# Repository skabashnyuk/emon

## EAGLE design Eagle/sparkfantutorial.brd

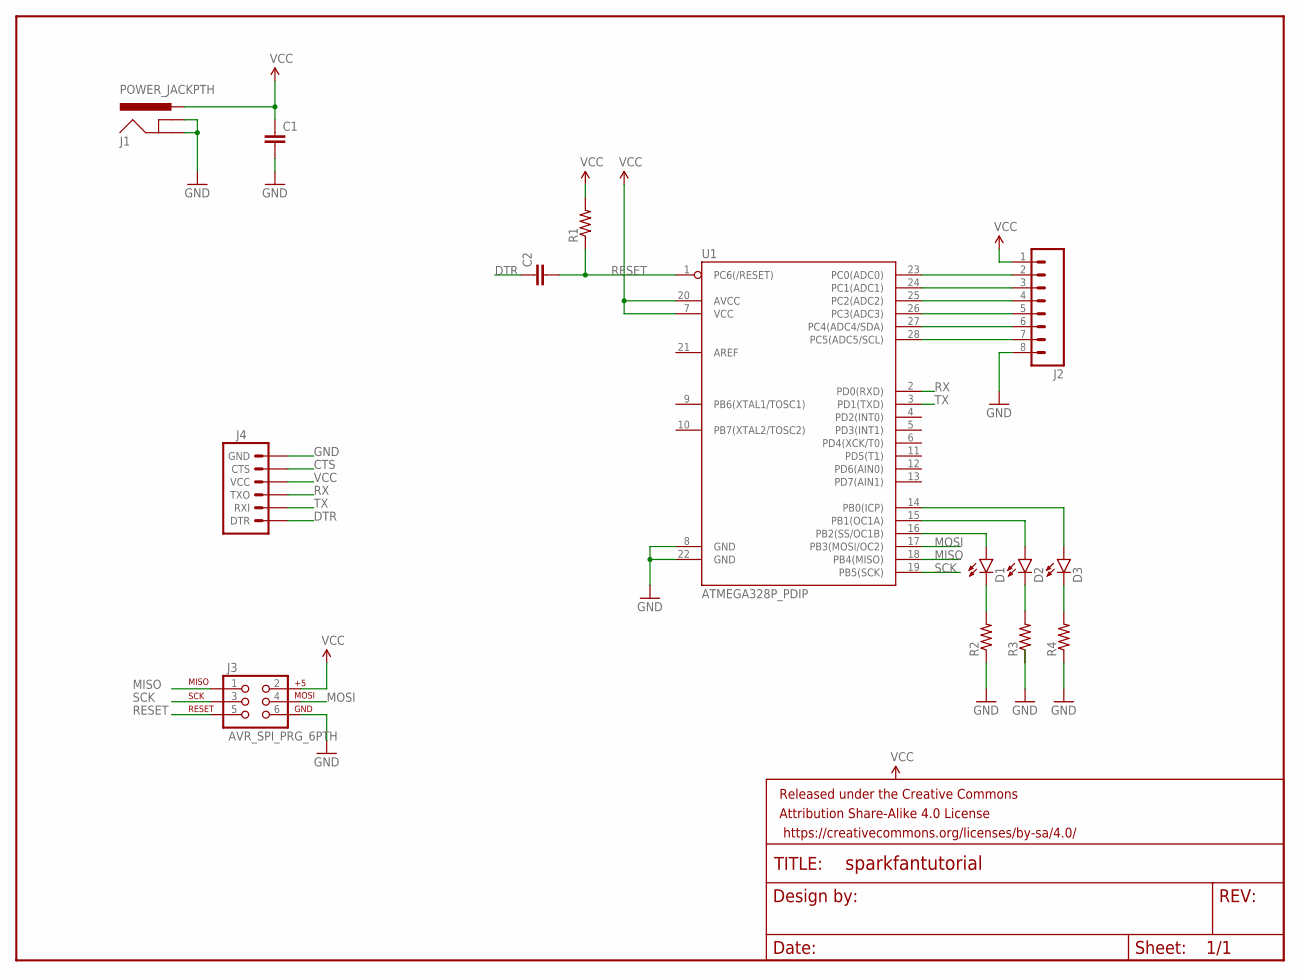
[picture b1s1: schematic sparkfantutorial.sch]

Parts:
C1, C2: CAPPTH; CAP-PTH-SMALL
D1, D2, D3: LED5MM
FRAME1: FRAME-LETTER; CREATIVE_COMMONS
J1: POWER_JACKPTH; POWER_JACK_PTH
J2: M08; 1X08_ROUND
J3: AVR_SPI_PRG_6PTH; 2X3
J4: ARDUINO_SERIAL_PROGRAMPTH; 1X06
R1, R2, R3, R4: RESISTORPTH-1/4W; AXIAL-0.4
U1: ATMEGA328P_PDIP; DIL28-3

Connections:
CTS: J4.5 (CTS)
DTR: C2.1, J4.1 (DTR)
GND: C1.2, J1.GND, J1.GNDBREAK, J2.8, J3.6, J4.6 (GND), R2.P$1 (1), R4.P$1 (1), U1.8 (GND), U1.22 (GND)
MISO: J3.1, U1.18 (PB4(MISO))
MOSI: J3.4, U1.17 (PB3(MOSI/OC2))
unnamed: D1.K (C), R2.P$2 (2)
unnamed: D1.A, U1.16 (PB2(SS/OC1B))
unnamed: D2.A, U1.15 (PB1(OC1A))
unnamed: D3.A, U1.14 (PB0(ICP))
unnamed: J2.2, U1.23 (PC0(ADC0))
unnamed: J2.3, U1.24 (PC1(ADC1))
unnamed: J2.4, U1.25 (PC2(ADC2))
unnamed: J2.5, U1.26 (PC3(ADC3))
unnamed: J2.6, U1.27 (PC4(ADC4/SDA))
unnamed: J2.7, U1.28 (PC5(ADC5/SCL))
unnamed: D2.K (C), R3.P$2 (2)
unnamed: D3.K (C), R4.P$2 (2)
RESET: C2.2, J3.5, R1.P$1 (1), U1.1 (PC6(/RESET))
RX: J4.3 (TXO), U1.2 (PD0(RXD))
SCK: J3.3, U1.19 (PB5(SCK))
TX: J4.2 (RXI), U1.3 (PD1(TXD))
VCC: C1.1, J1.PWR, J2.1, J3.2, J4.4 (VCC), R1.P$2 (2), U1.7 (VCC), U1.20 (AVCC)

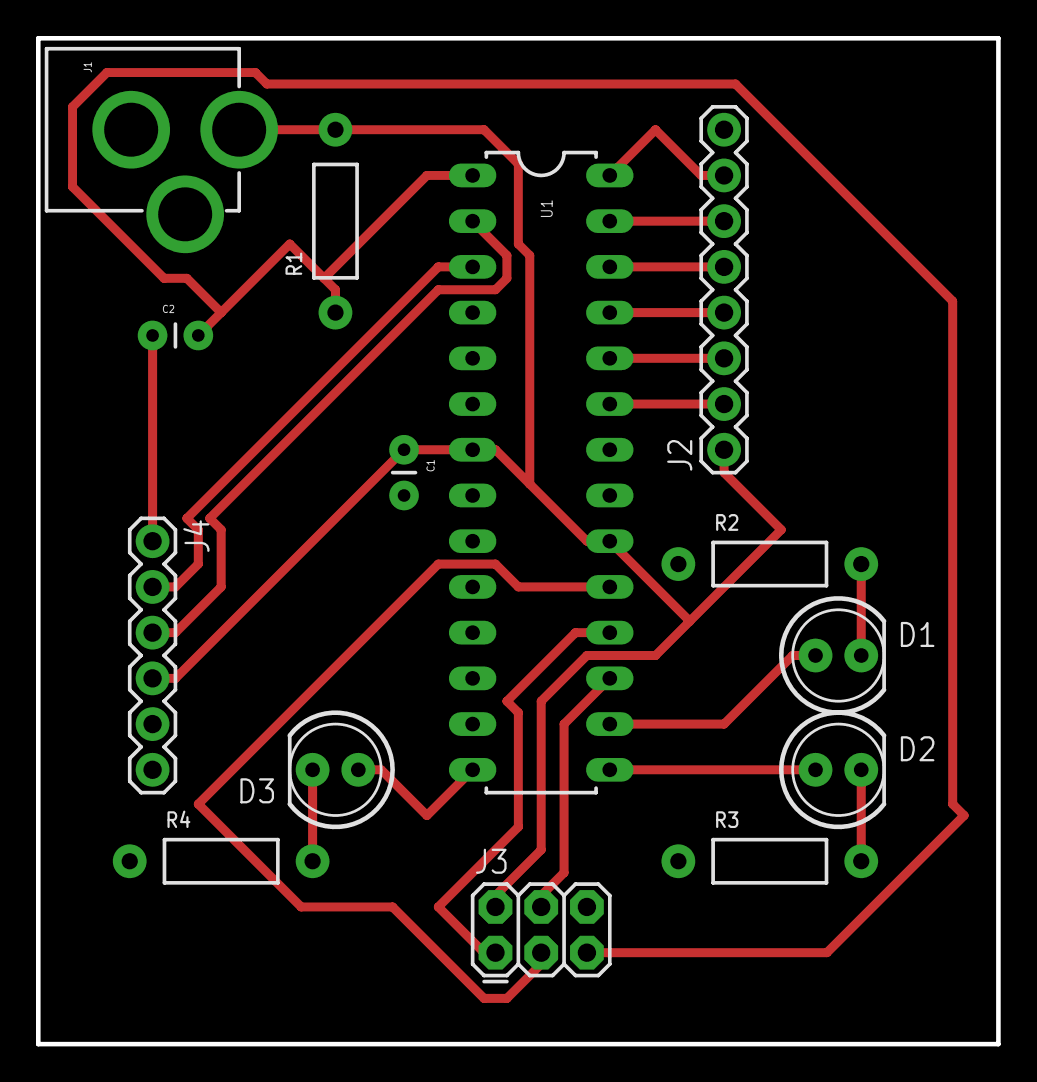
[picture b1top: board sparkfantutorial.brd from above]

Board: 2 copper layers, 53.3 x 55.9 mm, 15 parts (0 on the bottom side), 21 nets.

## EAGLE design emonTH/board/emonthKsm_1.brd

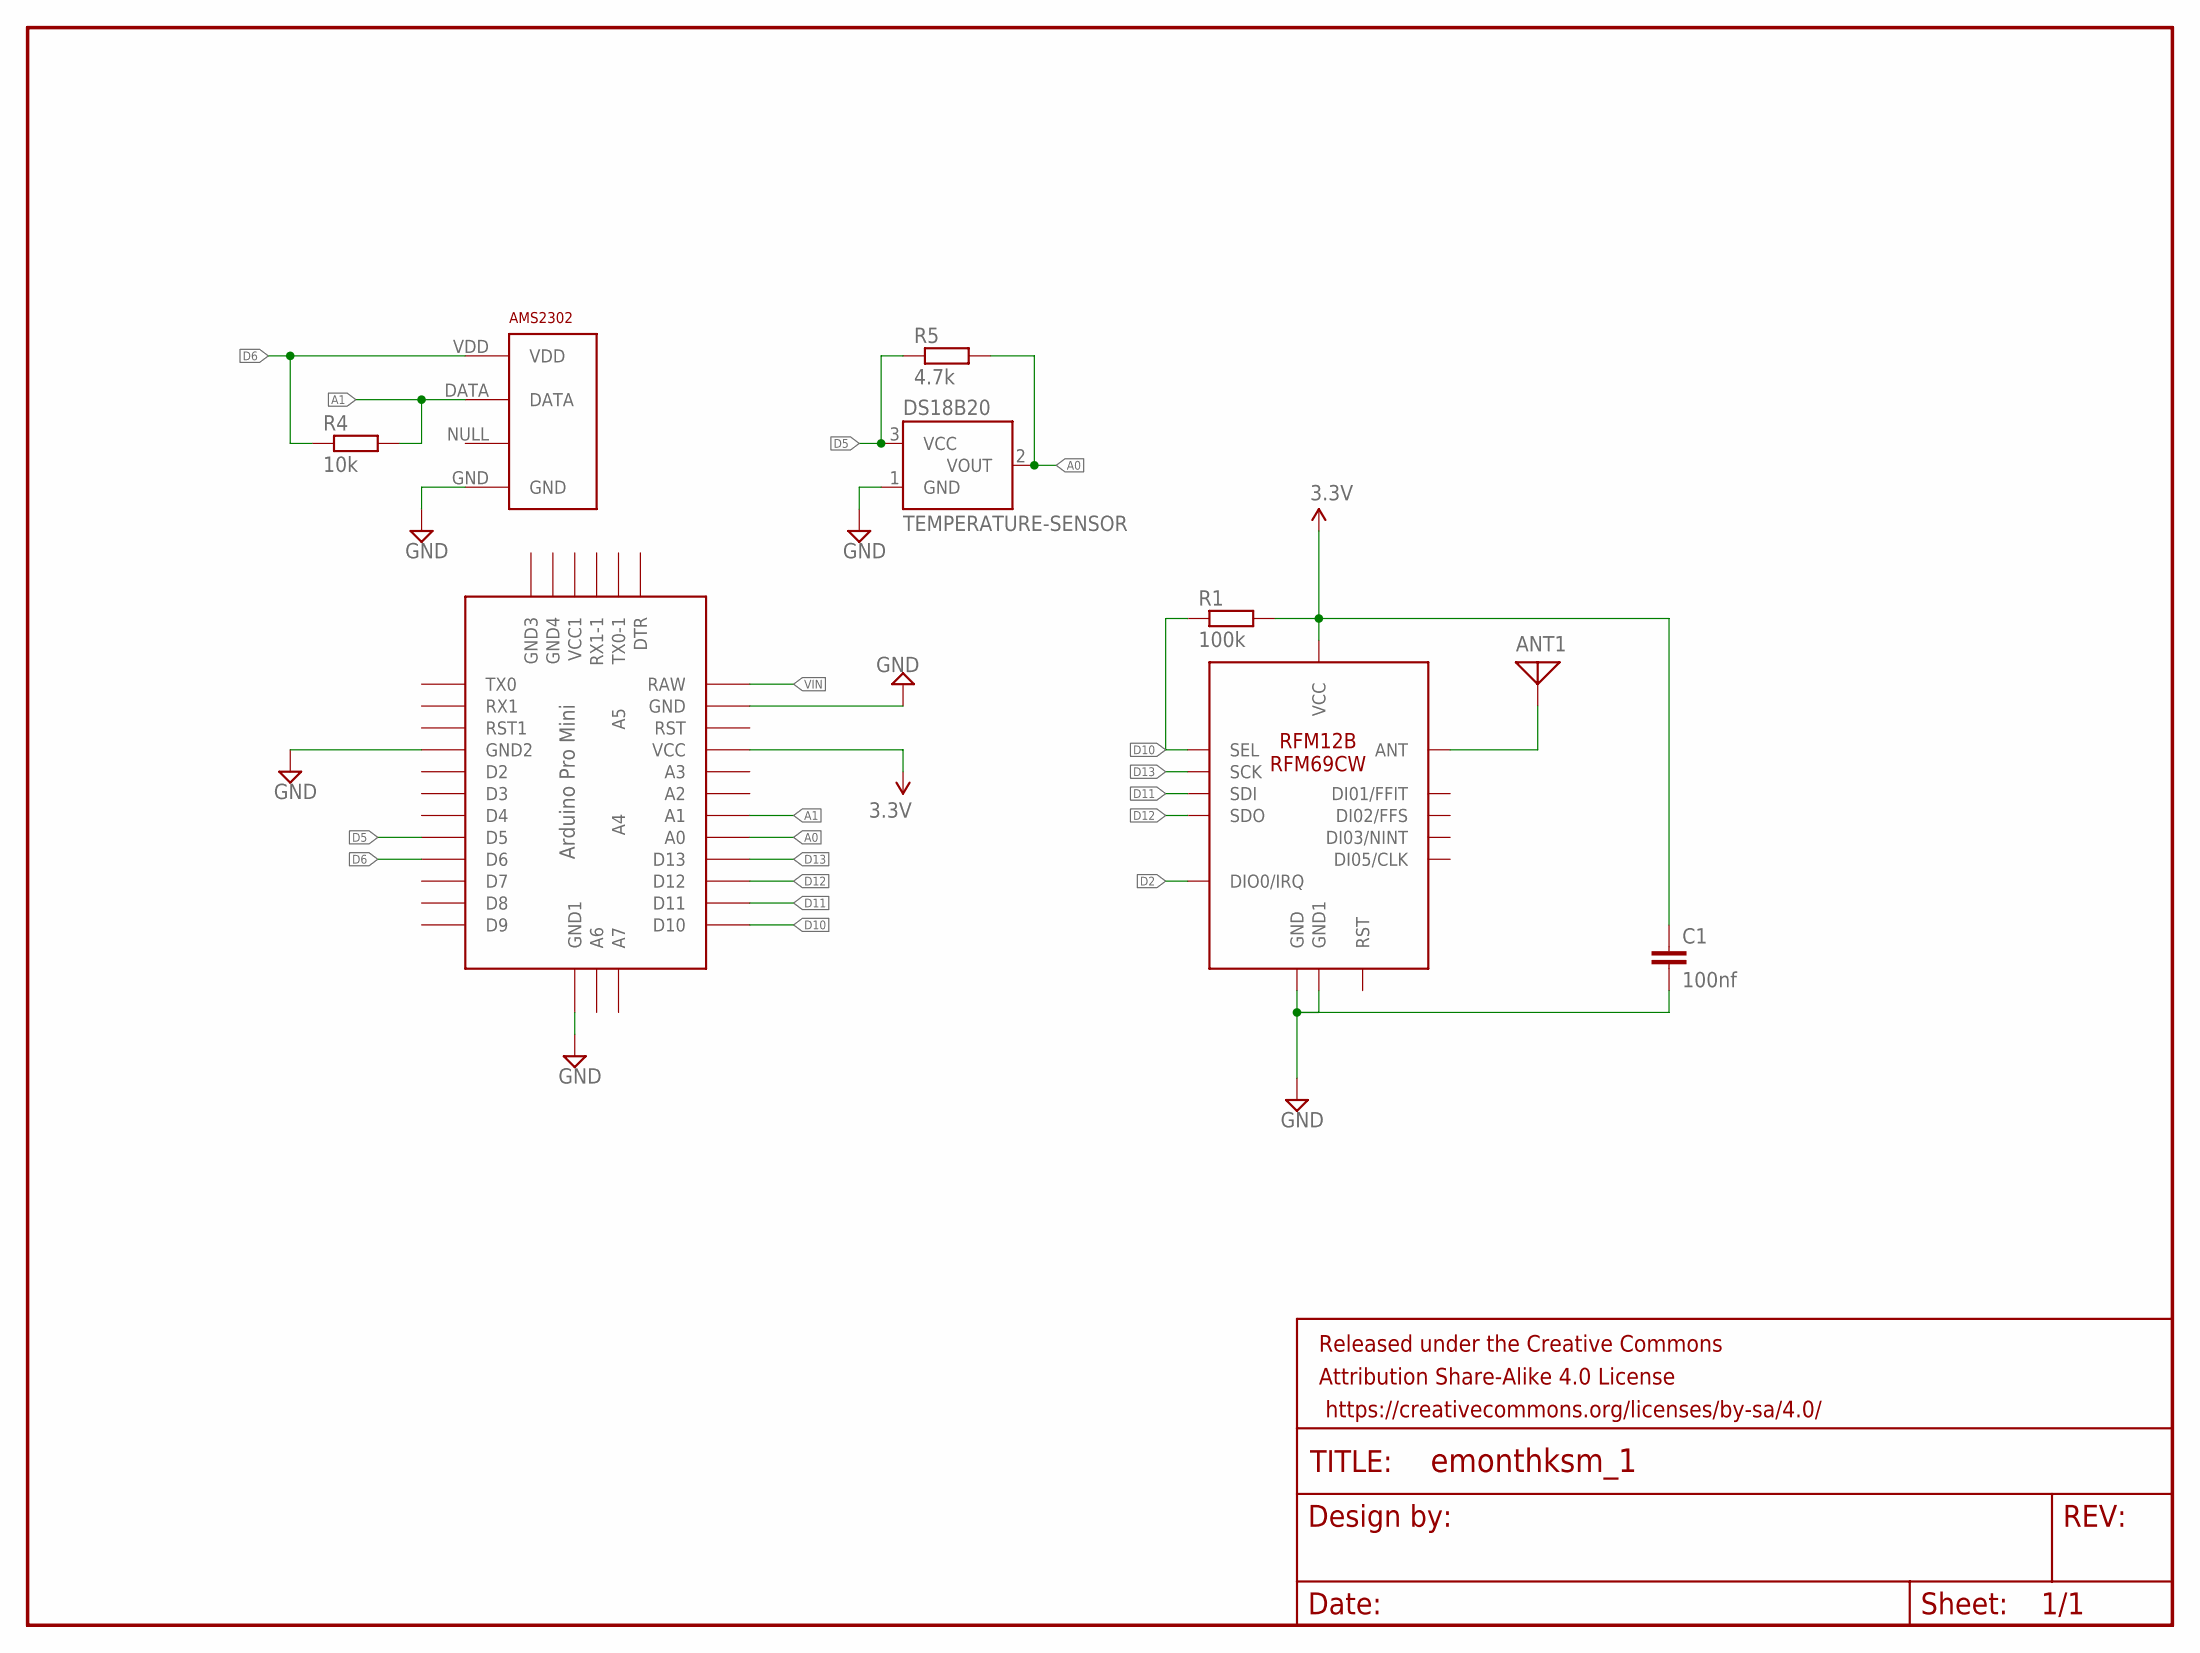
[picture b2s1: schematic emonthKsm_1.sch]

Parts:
AMS2302: RHT03_DHT-22_AM2302; RHT03_DHT-22
ANT1: ANTENNA; PAD-01
ARDUINO: ABK-PRO-MINI
C1: 100nf; C050-050X075
DS18B20: TEMPERATURE-SENSOR; TO-92
FRAME1: FRAME-LETTERNO_PACKAGE; DUMMY
R1: 100k; 0204/7
R4: 10k; 0204/7
R5: 4.7k; 0204/7
RFM69: RFM12B/69CW

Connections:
3.3V: ARDUINO.VCC, C1.1, R1.2, RFM69.VDD (VCC)
A0: ARDUINO.A0, DS18B20.2 (VOUT), R5.2
A1: AMS2302.DATA, ARDUINO.A1, R4.2
D2: RFM69.IRQ (DIO0/IRQ)
D5: ARDUINO.D5, DS18B20.3 (VCC), R5.1
D6: AMS2302.VDD, ARDUINO.D6, R4.1
D10: ARDUINO.D10, R1.1, RFM69.SEL
D11: ARDUINO.D11, RFM69.SDI
D12: ARDUINO.D12, RFM69.SDO
D13: ARDUINO.D13, RFM69.SCK
GND: AMS2302.GND, ARDUINO.GND, ARDUINO.GND1 (GND2), ARDUINO.GND4 (GND1), C1.2, DS18B20.1 (GND), RFM69.GND, RFM69.GND1
unnamed: ANT1.1, RFM69.ANT
VIN: ARDUINO.RAW

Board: 2 copper layers, 10 parts (0 on the bottom side), 11 nets, no tracks yet.

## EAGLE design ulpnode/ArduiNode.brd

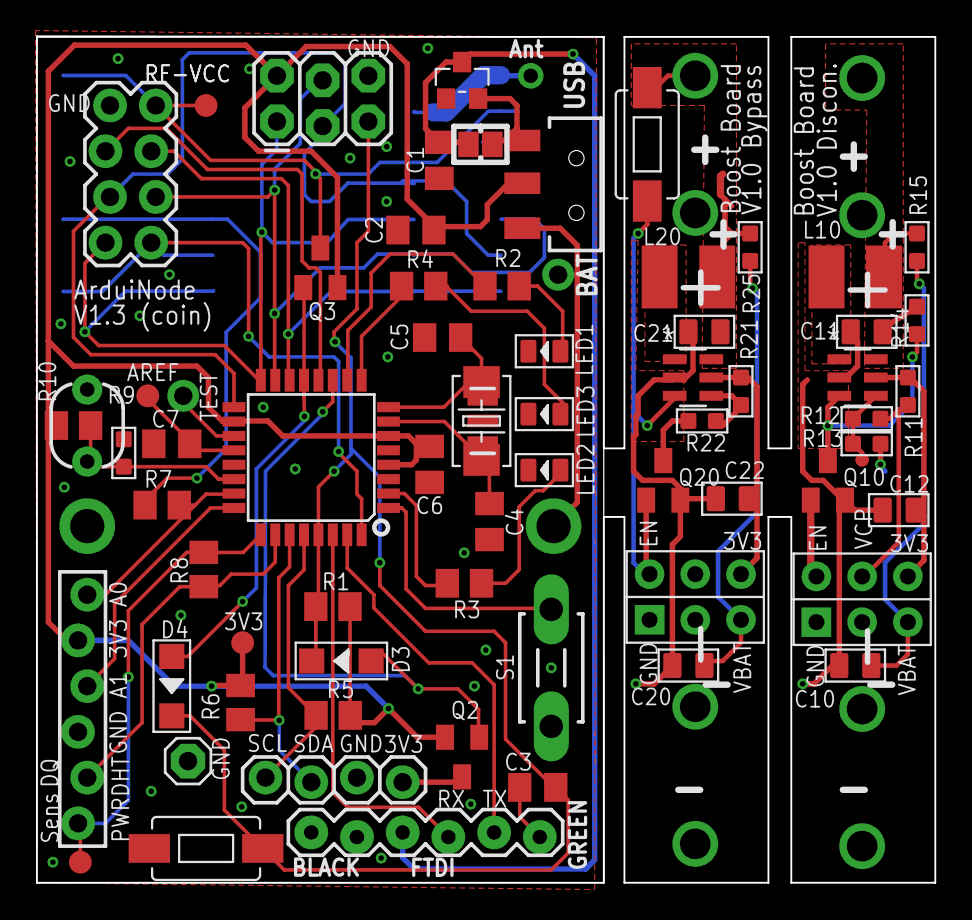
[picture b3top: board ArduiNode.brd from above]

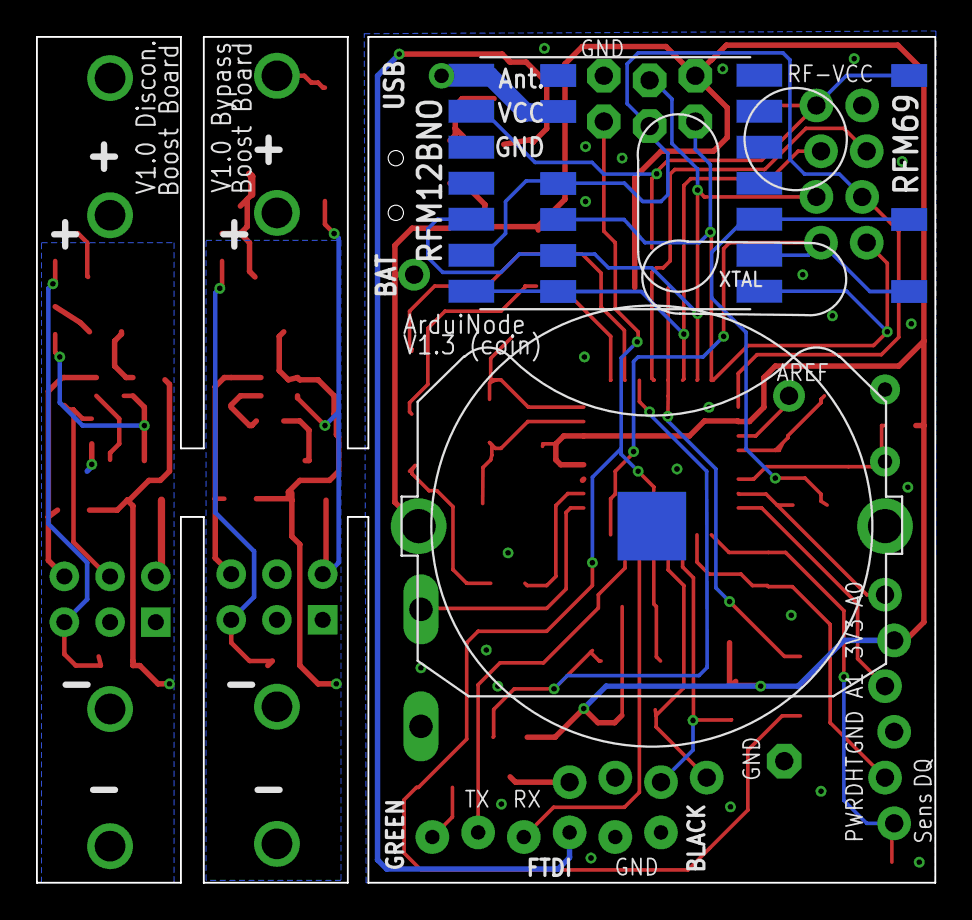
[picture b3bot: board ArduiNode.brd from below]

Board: 2 copper layers, 49.9 x 47.0 mm, 75 parts (3 on the bottom side), 56 nets.

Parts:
AAA-1, AAA-2: BATTERY-AAA-JL
C1: 1uF; C0805K
C2: 10uF; C0805K
C3, C6, C7: 0.1uF; C0805K
C4, C5: 22pF; C0805K
C10, C20: 1uF; C0805
C11, C12, C21, C22: 10uF; C0805
COIN_CLIP: CR2450; CR1220-THM
D3, D4: SOD123
EXT_PWR: 1X01-CLEANBIG
FTDI: 1X06-SIP_LOCK
I/O: 1X06_FEMALE_LOCK.010
IC10: MCP1640; SOT23-6
IC20: MCP1640C; SOT23-6
J1: ICSP; 2X3_LOCK
J2: JUMPER_SOLDER_1X2
J10, J20: PWR; 2X3P-2.54-2.54-11.6-3.0-BLACK-MALE
L10, L20: 4.7uH; L1812
LED1, LED2, LED3: LED-0805
Q2, Q3: BSS84; SOT23
Q10: NDS7002A; SOT23
Q20: FDN337N; SOT23
R1: 10k; M0805
R2, R3, R4: 1K; M0805
R5, R6, R8: 4.7K; M0805
R7: 100; M0805
R9: PHOTOCELL
R10: 10K; M0805
R11: 953K; R0603
R12: 270K; R0603
R13, R22: 680K; R0603
R14: 1M; R0603
R15, R25: 1K; R0603
R21: 1M21; R0603
RFM12B: RFM12BNO; RFM12B
S1: DTS-3
S2: RESET; TACTILE-SWITCH-1101NE
S21: Start; TACTILE-SWITCH-1101NE
SW1: USB_COIN; SWITCH-SPDT-SMD
TEST: 1X01-CLEANBIG
THERMISTOR: 10K; R0603
TP1: 1X01
TP2, TP3, TP4, TP5: TEST-POINT3X5; PAD.03X.05
TP6: TEST-POINT3; PAD.03X.03
U1: XC6206-3.3; SOT23
U2: ATMEGA328P; TQFP32
U$3: OLED; 1X04_LOCK
U$4: NRF24; 2X04_LOCK
U$11: RFM12B_ANTENNA; RFM12B-ANTENNA
X2: 16MHz; 2P-SMD-5.0X3.2
X3: RFM69; RFM69W-MINPADS
Y1: 16MHz; RESONATOR-SMD

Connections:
+3V3: C2.1, C6.2, I/O.5, J1.2, Q2.2, Q3.2, R1.2, R5.2, R6.2, R10.2, SW1.2, TP2.P$1, U2.4, U2.6, U2.18
A0: I/O.6, R7.1, U2.23
A1: I/O.4, U2.24
AGND10: AAA-1.GND@1, C10.1, C11.1, C12.1, IC10.2, J10.1, Q10.2, R13.1
AGND20: AAA-2.GND@1, C20.1, C21.1, C22.1, IC20.2, J20.1, Q20.2
ANT: RFM12B.ANT, U$11.P$1, X3.ANT
AREF: C7.1, TP3.P$1, U2.20
BYPASS: IC20.3, J20.6, Q20.1, S21.P$1
DHT/DQ: I/O.2, R8.1, U2.26
DTR: C3.1, FTDI.6
EN: IC10.3, Q10.3, R14.1
ENABLE: J10.6, Q10.1
GND: C1.2, C2.2, C4.2, C5.2, C6.1, C7.2, COIN_CLIP.GND, FTDI.1, FTDI.2, I/O.3, J1.6, LED1.-, LED2.-, LED3.-, R9.1, RFM12B.GND, S1.2, S2.P$1, THERMISTOR.1, TP1.1, U1.1, U2.3, U2.5, U2.21, U$3.2, U$4.GND, X3.GND, Y1.2
GRN_LED: R4.2, U2.9
I2C_PWR: D3.+, Q2.1, U2.11
LIGHT: R9.2, R10.1, THERMISTOR.2, U2.22
MISO: J1.1, RFM12B.SDO, U2.16, U$4.MISO, X3.MISO
MOSI: J1.4, RFM12B.SDI, U2.15, U$4.MOSI, X3.MOSI
unnamed: R7.2, RFM12B.FFS, X3.DIO2
unnamed: LED1.+, R2.1
unnamed: LED2.+, R3.1
unnamed: LED3.+, R4.1
unnamed: Q20.3, R22.1
unnamed: Q2.3, U$3.1
RED_LED: R2.2, U2.10
RESET: C3.2, D3.-, D4.-, J1.5, R1.1, S2.P$2, U2.29
RF-VCC: Q3.3, RFM12B.VDD, TP5.P$1, U$4.PWR, X3.VDD
RFCE: U2.12, U$4.CE
RFCSN: RFM12B.SEL, U2.14, U$4.CSN, X3.NSS
RFIRQ: RFM12B.IRQ, U2.32, U$4.IRQ, X3.DIO0
RFPWR: D4.+, Q3.1, U2.13
RXI: FTDI.4, U2.30
SCK: J1.3, RFM12B.SCK, U2.17, U$4.SCK, X3.SCK
SCL: R5.1, U2.28, U$3.4
SDA: R6.1, U2.27, U$3.3
SENSOR_PWR: I/O.1, R8.2, TP4.P$1, U2.25
SW: IC10.1, L10.2
SW20: IC20.1, L20.2
SWIRQ: S1.1, U2.1
TEST: TEST.1, U2.19
TXO: FTDI.5, U2.31
VABAT10: C10.2, J10.3, R15.1
VABAT20: C20.2, J20.3, R25.1
VBAT: COIN_CLIP.+1, EXT_PWR.1, SW1.1
VBAT10: AAA-1.PWR@1, C11.2, IC10.6, L10.1, R14.2, R15.2
VBAT20: AAA-2.PWR@1, C21.2, IC20.6, L20.1, R25.2, S21.P$2
VCP: J10.5, R11.1, R12.2
VFB10: IC10.4, R12.1, R13.2, TP6.P$1
VFB20: IC20.4, R21.1, R22.2
VOUT10: C12.2, IC10.5, J10.4, R11.2
VOUT20: C22.2, IC20.5, J20.4, R21.2
VREG: J2.1, SW1.3, U1.2
VUSB: C1.1, FTDI.3, J2.2, U1.3
X1: C5.1, U2.8, X2.1, Y1.3
XTAL1: C4.1, U2.7, X2.2, Y1.1
YEL_LED: R3.2, U2.2

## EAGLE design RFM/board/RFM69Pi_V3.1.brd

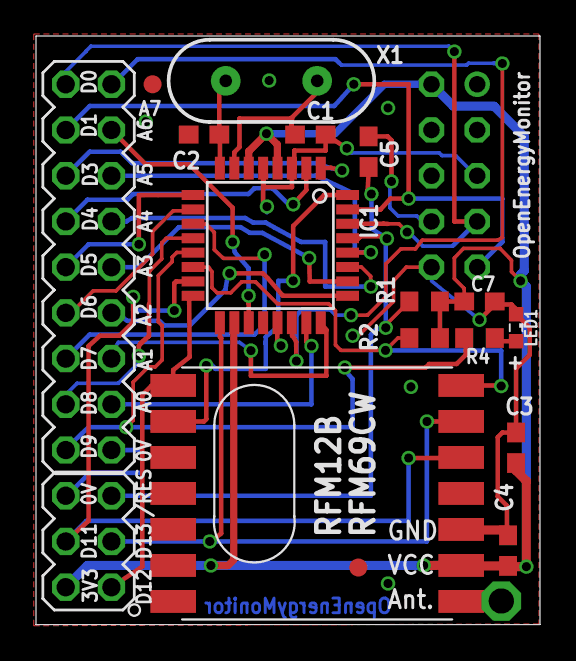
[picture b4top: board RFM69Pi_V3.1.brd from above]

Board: 2 copper layers, 28.0 x 32.7 mm, 18 parts (0 on the bottom side), 30 nets.

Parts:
ANT1: PAD-01
C1, C2: 22pF; C0603
C3: 10uF; C0603
C4, C5, C7: 0.1uF; C0603
GPIO_1: FE05-2
IC1: ATMEGA168; TQFP32-08
LED1: SML0603
PL2: MA12-2
R1, R2: 10K; R0603
R4: 1K; R0603
RFM12B-RFM69CW: RFM12B
U$1, U$2: FIDUCIAL; FIDUCIAL_1MM
X1: HC49US

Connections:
+3V3: C3.2, C4.1, C7.1, GPIO_1.2, IC1.4, IC1.6, IC1.18, PL2.2, R1.2, R2.2, RFM12B-RFM69CW.VDD
A0: IC1.23, PL2.9
A1: IC1.24, PL2.11
A2: IC1.25, PL2.13
A3: IC1.26, PL2.15
A4/SDA: IC1.27, PL2.17
A5/SCL: IC1.28, PL2.19
A6: IC1.19, PL2.21
A7: IC1.22, PL2.23
D0/RX: GPIO_1.7, IC1.30, PL2.24
D1/TX: GPIO_1.9, IC1.31, PL2.22
D2: IC1.32, RFM12B-RFM69CW.IRQ
D3: IC1.1, PL2.20
D4: IC1.2, PL2.18
D5: IC1.9, PL2.16
D6: IC1.10, PL2.14
D7: IC1.11, PL2.12
D8: IC1.12, PL2.10
D9: IC1.13, PL2.8, R4.2
D10: IC1.14, R2.1, RFM12B-RFM69CW.SEL
D11/MOSI: IC1.15, PL2.4, RFM12B-RFM69CW.SDI
D12/MISO: IC1.16, PL2.1, RFM12B-RFM69CW.SDO
D13/SCK: IC1.17, PL2.3, RFM12B-RFM69CW.SCK
GND: C1.2, C2.2, C3.1, C4.2, C7.2, GPIO_1.5, GPIO_1.10, IC1.3, IC1.5, IC1.21, LED1.C, PL2.6, PL2.7, RFM12B-RFM69CW.GND
unnamed: C1.1, IC1.7, X1.2
unnamed: C2.1, IC1.8, X1.1
unnamed: LED1.A, R4.1
unnamed: ANT1.1, RFM12B-RFM69CW.ANT
RESET: C5.2, IC1.29, PL2.5, R1.1
_RESET: C5.1, GPIO_1.8

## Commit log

2016-03-16 Init
2016-03-18 Add OSX specific ignore
2016-03-18 Added EMonth
2016-03-18 Added seed configs
2016-03-18 Added more eagle ingnore
2016-03-18 Used seed dru
2016-05-10 Code reorganize
2016-05-15 Added new board
2016-05-15 Fritzing
2016-05-15 Added board
2016-05-15 Replaced smd components with regular
2016-05-26 Added ULP node
2016-05-26 Used seeed dru
2016-06-07 Added gerber of ArduiNode
2016-06-07 Update emonthKSM board
2016-06-07 Added sparkfan tutorial board
2016-06-07 Added RMF test firmware
2016-06-12 Add RFM69 gerber
2016-08-07 Added gerber of emonth 1.5.2
2016-08-07 emonth board cleanup
2016-08-07 Added elecrow gerber generator
2016-08-07 added EmonTX 3.4.1
2016-08-07 Sync with upstream
2016-08-19 Send more accurate battery voltage

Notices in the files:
parts and their libraries:
SparkFun-Capacitors: Licensing: Creative Commons ShareAlike 4.0 International - https://creativecommons.org/licenses/by-sa/4.0
SparkFun-Aesthetics: Released under the Creative Commons Attribution Share-Alike 4.0 License
SparkFun-Aesthetics: https://creativecommons.org/licenses/by-sa/4.0
